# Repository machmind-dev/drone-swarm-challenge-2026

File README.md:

**Team** · [machmind.dev](http://machmind.dev)

| Member | Disciplines |
|--------|-------------|
| [**Mindaugas Jonauskis**](https://www.linkedin.com/in/mindaugas-jonauskis-11931145/) (Founder) | Firmware & Software Engineering · Electronics & Electrical Design |
| [**Hauke Renk**](https://www.linkedin.com/in/hauke-renk-90832739a/) | Mechanical Design & Integration |

---

# Swarm Drone Challenge 2026

Source code of the solution by **Team Mach Mind** for the [Swarm Drone Challenge 2026](https://swarmdronechallenge.digital/), organised by [MBDA](https://www.mbda-systems.com) and [brigkAIR](https://www.brigk.digital/en/brigkair/).

Qualifying rounds took place **20–24 April 2026**. Team Mach Mind qualified as one of **6 finalists** and finished **4th place** at the Finals on **11 June 2026** at ILA Berlin.

<p align="center"></p>

**Drone Versions**

| Version | Event | MCU | CPU (MHz), PSRAM (MB) | ToF | Vision | ArUco |
|---------|-------|-----|-------|-----|--------|-------|
| [v1.0](drone-firmware/v1.0/) | Qualifying | S3 | 240 MHz, 8 MB | 4 | Offboard | 80×60px, up to 4 m |
| [v2.0](drone-firmware/v2.0/) | Finals | S3&P4 | 240&360 MHz, 8&32 MB | 6 | Onboard | 320×240px, up to 12 m |

## System Architecture (v2.0)

---

## Swarm Behaviour

The **SDC26 Commander** (`ground-station-software/swarm/sdc26_commander.py`) runs the swarm by role, streaming waypoints to `/gcs/drone_<id>/control` in the arena frame (`id · x · y · height`).

**Swarm control via LLM — demo only:** Ollama (Gemma) turns natural-language instructions into JSON/coordinate commands, but it is a standalone DEMO and is NOT in live on the finals. Meaningful coordinate tasking needs a reliable absolute position reference (ArUco Navigation), which we couldn't be fully implement in time, so all live flight is run by the deterministic Commander above.

**Waypoint execution (Manhattan):** the firmware converts each arena waypoint to NED and reaches it in axis-aligned legs (one axis at a time, no diagonals), each leg flown as a sequence of discrete steps — keeping motion predictable and obstacle handling simple.

| Role | Behaviour |
|------|-----------|
| **Executor** | Captures opponent boxes based on locations received from a Seeker. |
| **Seeker** | The only role that publishes box locations. If a box is not found within 2 minutes, the GCS publishes a random. |
| **Leader** | Monitors the home base while no boxes have been captured. |

---

## Repository Structure

```
drone-swarm-challenge-2026/
├── drone-firmware/          # All drone onboard firmware (v1.0 and v2.0)
│   ├── v1.0/                # SDC 2026 Qualifying — single ESP32-S3
│   └── v2.0/                # SDC 2026 Finals — dual ESP32-P4 + ESP32-S3
│       ├── drone-vision-esp32p4/  # Navigation: ArUco, ToF, UART TX
│       ├── drone-comms-esp32s3/   # Communication: MAVLink, micro-ROS
│       └── shared/                # Binary UART protocol header
├── ground-station-software/ # ROS2 ground control station, swarm algorithms & vision
├── hardware/                # Mechanical and electrical design files
├── launchers/               # Platform-specific launch scripts
│   ├── ubuntu-gnome-pc/     # x86_64 Ubuntu GNOME (development GCS)
│   └── ubuntu-xfce-pi5/     # ARM64 Raspberry Pi 5 (field GCS)
└── docs/                    # Documentation and media
```

---

## To Do

### Navigation

- [x] **Manhattan waypoint navigation** (`drone-firmware/v2.0/drone-comms-esp32s3/main/main.c`) — 1 m steps X-leg first then Y-leg; yaw to face travel direction; ToF obstacle stop at 500 mm; awaits new GCS command on obstacle; keyboard pass-through for steps ≤ 1 m; arrival tolerance 1 m. Since navigation via ArUco markers were not implemented a work around took place.

### Calibration

- [ ] **Full ChArUco calibration on ESP32-P4** (`drone-firmware/v2.0/drone-vision-esp32p4/`) — barrel distortion not yet corrected. Current focal-length correction (fx=438.6 px) achieves ~1% range error but sub-cm accuracy requires a full calibration run with a ChArUco board.

---

## Open Issues

### ArUco navigation

ArUco-based EKF fusion was developed, but not fully deployed in time for the finals. ArUco is therefore used only for box detection, not navigation.

---

## Hardware

### Drone Version 2.0

| Swarm Stack Bracket | Base for LiDAR & Flow Motion | FC adapter 25.5 to 20 mm |
|---|---|---|
|  |  |  |

| Swarm Stack PCB | Spoiler Block (for RFID) | Spoiler Block Bracket |
|---|---|---|
|  |  |  |

---

Drones assembled and ready for first flight test as formation of five units

<table><tr>
<td></td>
<td></td>
<td></td>
</tr><tr>
<td></td>
<td></td>
<td></td>
</tr><tr>
<td></td>
<td></td>
<td></td>
</tr></table>

---

### Ground Control Station

| Bezel Mk2 | Panel Bottom | Bottom Frame Mk2 |
|---|---|---|
|  |  |  |

| Exhaust | Top Connector | Top Lower LH Mk3 |
|---|---|---|
|  |  |  |

| Top Lower RH Mk3 | Top Upper LH Mk3 | Top Upper RH Mk3 |
|---|---|---|
|  |  |  |

Ground Control Station assembled and in use for flight testing

| Monitor trial fit | Assembling 1 | Assembling 2 |
|---|---|---|
|  |  |  |

---

### Transportation

| Transport Box Version 2.0 | Transport Box Version 1.0 |
|---|---|
|  |  |

---

Drones packed for trip to ILA Berlin 2026

---

## License

This project is licensed under the [MIT License](LICENSE).

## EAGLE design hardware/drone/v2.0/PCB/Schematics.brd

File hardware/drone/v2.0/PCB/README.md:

# Swarm Stack PCB

Schematics and board design: **Autodesk Eagle** (`.sch` / `.brd`)

<table><tr>
<td></td>
<td></td>
</tr></table>

## ToF Sensors (VL53L1X)

| Sensor | XSHUT GPIO | Direction |
|--------|------------|-----------|
| S0 | GPIO4 | Left Hand (LH) |
| S1 | GPIO20 | LH 45° |
| S2 | GPIO21 | Forward |
| S3 | GPIO26 | 45° RH |
| S4 | GPIO32 | Right Hand (RH) |
| S5 | GPIO27 | Upwards |

## I2C (ESP32-P4)

| Signal | GPIO |
|--------|------|
| SDA | GPIO2 |
| SCL | GPIO3 |

**Note 1:** The 1K Ohm current limiting resistor for LED strip control is not populated on the PCB — add it externally on the signal line.

**Note 2:** BEC must share a common ground with the Swarm Stack.

**Note 3:** Pinout was modified in the latest version — Waveshare ESP32-P4 with and without WiFi module have different pinouts.

**Note 4:** C6 module with WiFi 6 is not used and meant for the future.

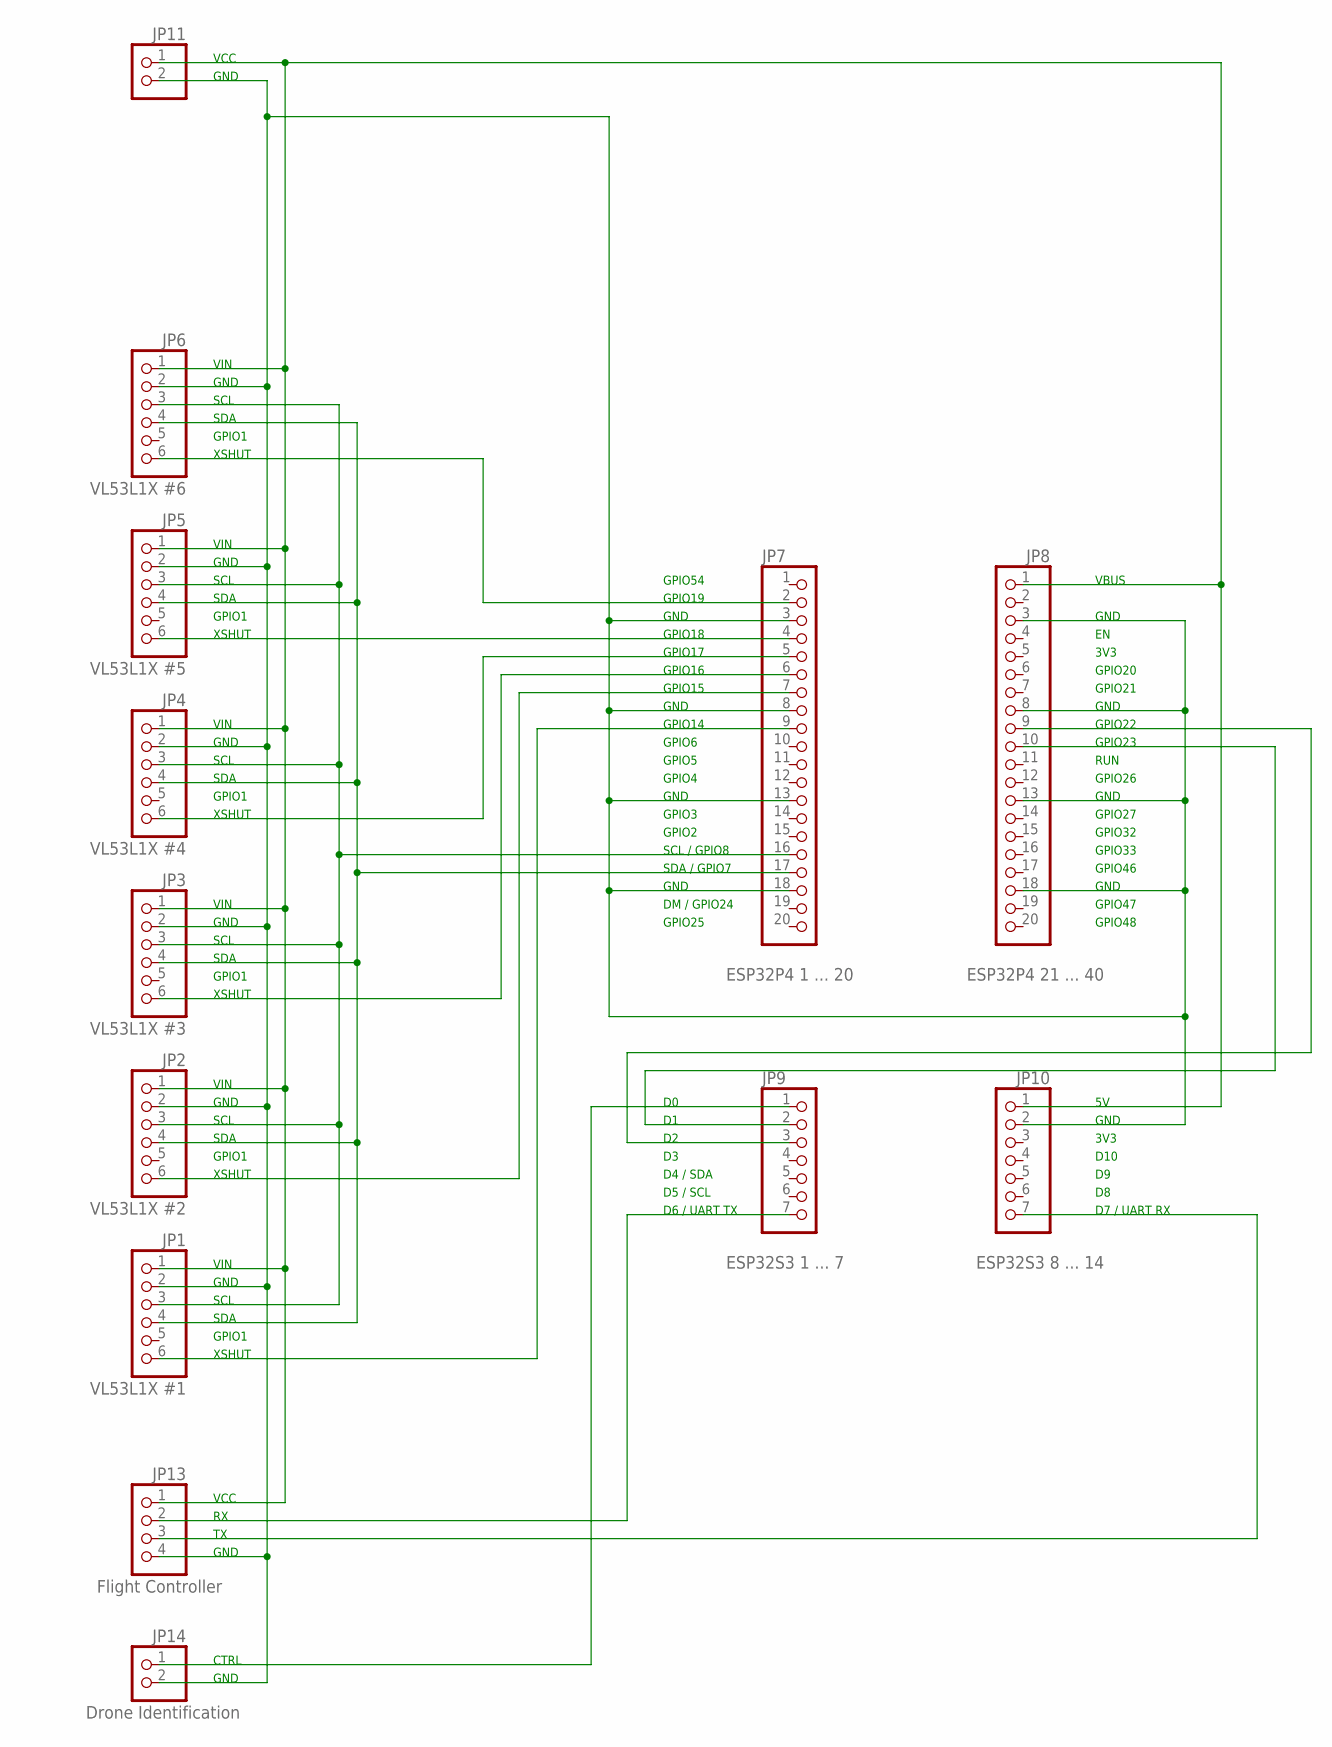
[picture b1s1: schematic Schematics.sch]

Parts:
JP1: VL53L1X #1; 1X06
JP2: VL53L1X #2; 1X06
JP3: VL53L1X #3; 1X06
JP4: VL53L1X #4; 1X06
JP5: VL53L1X #5; 1X06
JP6: VL53L1X #6; 1X06
JP7: ESP32P4 1 ... 20; 1X20
JP8: ESP32P4 21 ... 40; 1X20
JP9: ESP32S3 1 ... 7; 1X07
JP10: ESP32S3 8 ... 14; 1X07
JP11: PINHD-1X2; 1X02
JP13: Flight Controller; 1X04
JP14: Drone Identification; 1X02

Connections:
5VDC: JP1.1, JP2.1, JP3.1, JP4.1, JP5.1, JP6.1, JP8.1, JP10.1, JP11.1, JP13.1
GND: JP1.2, JP2.2, JP3.2, JP4.2, JP5.2, JP6.2, JP7.3, JP7.8, JP7.13, JP7.18, JP8.3, JP8.8, JP8.13, JP8.18, JP10.2, JP11.2, JP13.4, JP14.2
LED_CTRL: JP9.1, JP14.1
MASTER_RX: JP8.10, JP9.2
MASTER_TX: JP8.9, JP9.3
MAVLINK_RX: JP10.7, JP13.3
MAVLINK_TX: JP9.7, JP13.2
SCL: JP1.3, JP2.3, JP3.3, JP4.3, JP5.3, JP6.3, JP7.16
SDA: JP1.4, JP2.4, JP3.4, JP4.4, JP5.4, JP6.4, JP7.17
XSHUT1: JP1.6, JP7.9
XSHUT2: JP2.6, JP7.7
XSHUT3: JP3.6, JP7.6
XSHUT4: JP4.6, JP7.5
XSHUT5: JP5.6, JP7.4
XSHUT6: JP6.6, JP7.2

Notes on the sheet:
VIN
GND
SCL
SDA
GPIO1
XSHUT
GPIO54
GPIO19
GPIO18
GPIO17
GPIO16
GPIO15
GPIO14
GPIO6
GPIO5
GPIO4
GPIO3
GPIO2
SCL / GPIO8
SDA / GPIO7
DM / GPIO24
GPIO25
VBUS
GPIO20
3V3
GPIO21
GPIO22
GPIO23
RUN
GPIO26
GPIO27
GPIO32
GPIO33
GPIO46
GPIO47
GPIO48
D4 / SDA
D5 / SCL
D6 / UART TX
D10

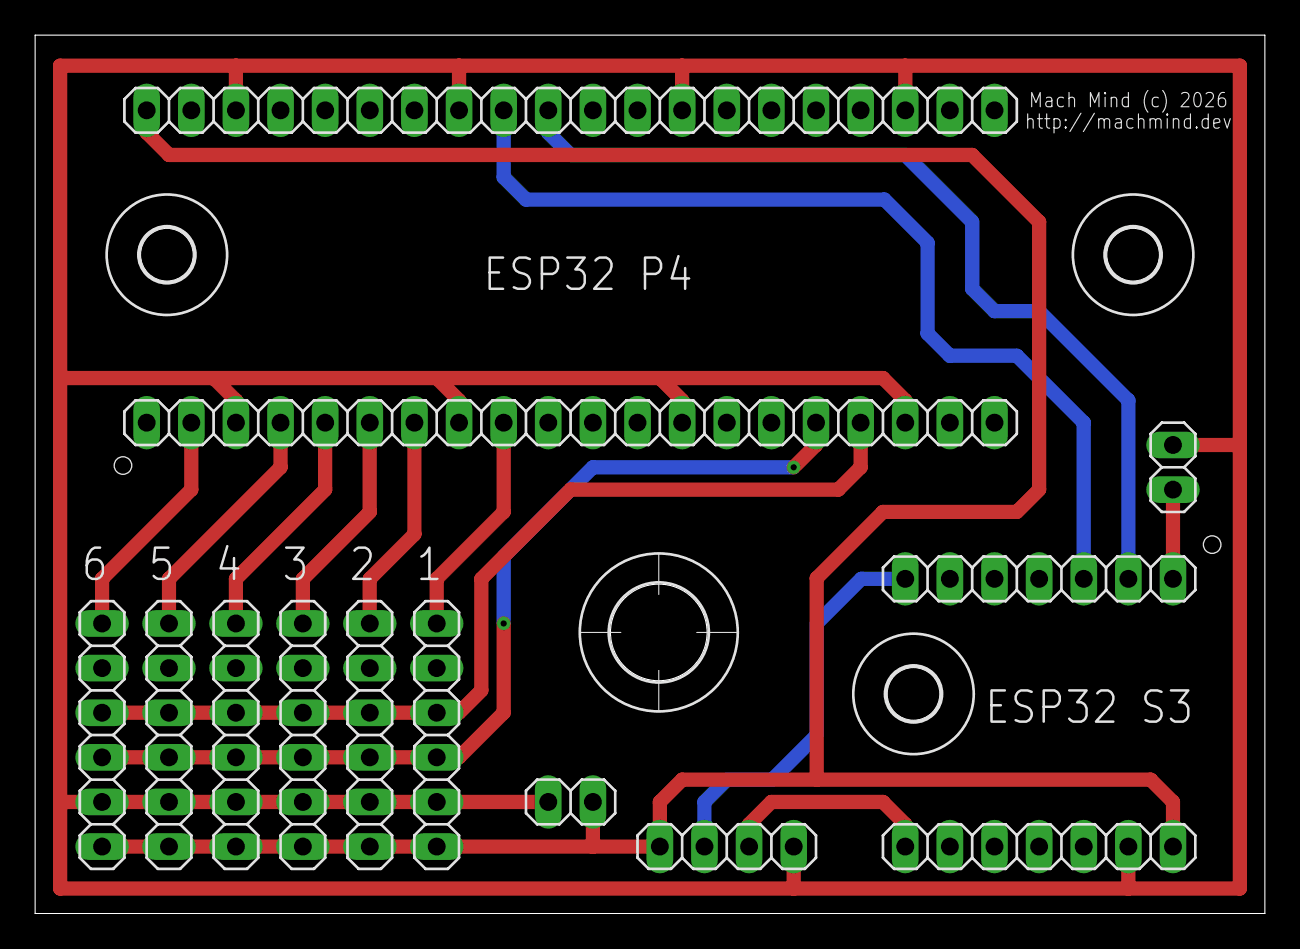
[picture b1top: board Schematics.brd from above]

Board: 2 copper layers, 70.0 x 50.0 mm, 17 parts (0 on the bottom side), 15 nets.

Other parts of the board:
U$1, U$2, U$3: 3,0
U$4: 5,5

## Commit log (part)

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2026-06-03 Revert "docs(readme): rename column to CPU (MHz) / PSRAM (MB), remove units from cells"
    This reverts commit 98dc004b87094fea51a2edf94ea27a0591241f70.
2026-06-03 Revert "docs(readme): remove spaces around & in v2.0 table cells"
    This reverts commit a6ee924a8e47d757c7a99d55a8a422f02959e478.
2026-06-09 Revert "docs(hardware): move v2.0 PCB photo inside comparison table"
    This reverts commit aeaee8f319c36baea5a87a6bfd99ee73ab40f1a1.

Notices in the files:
hardware/drone/v2.0/PCB/Schematics.brd:
Mach Mind (c) 2026
